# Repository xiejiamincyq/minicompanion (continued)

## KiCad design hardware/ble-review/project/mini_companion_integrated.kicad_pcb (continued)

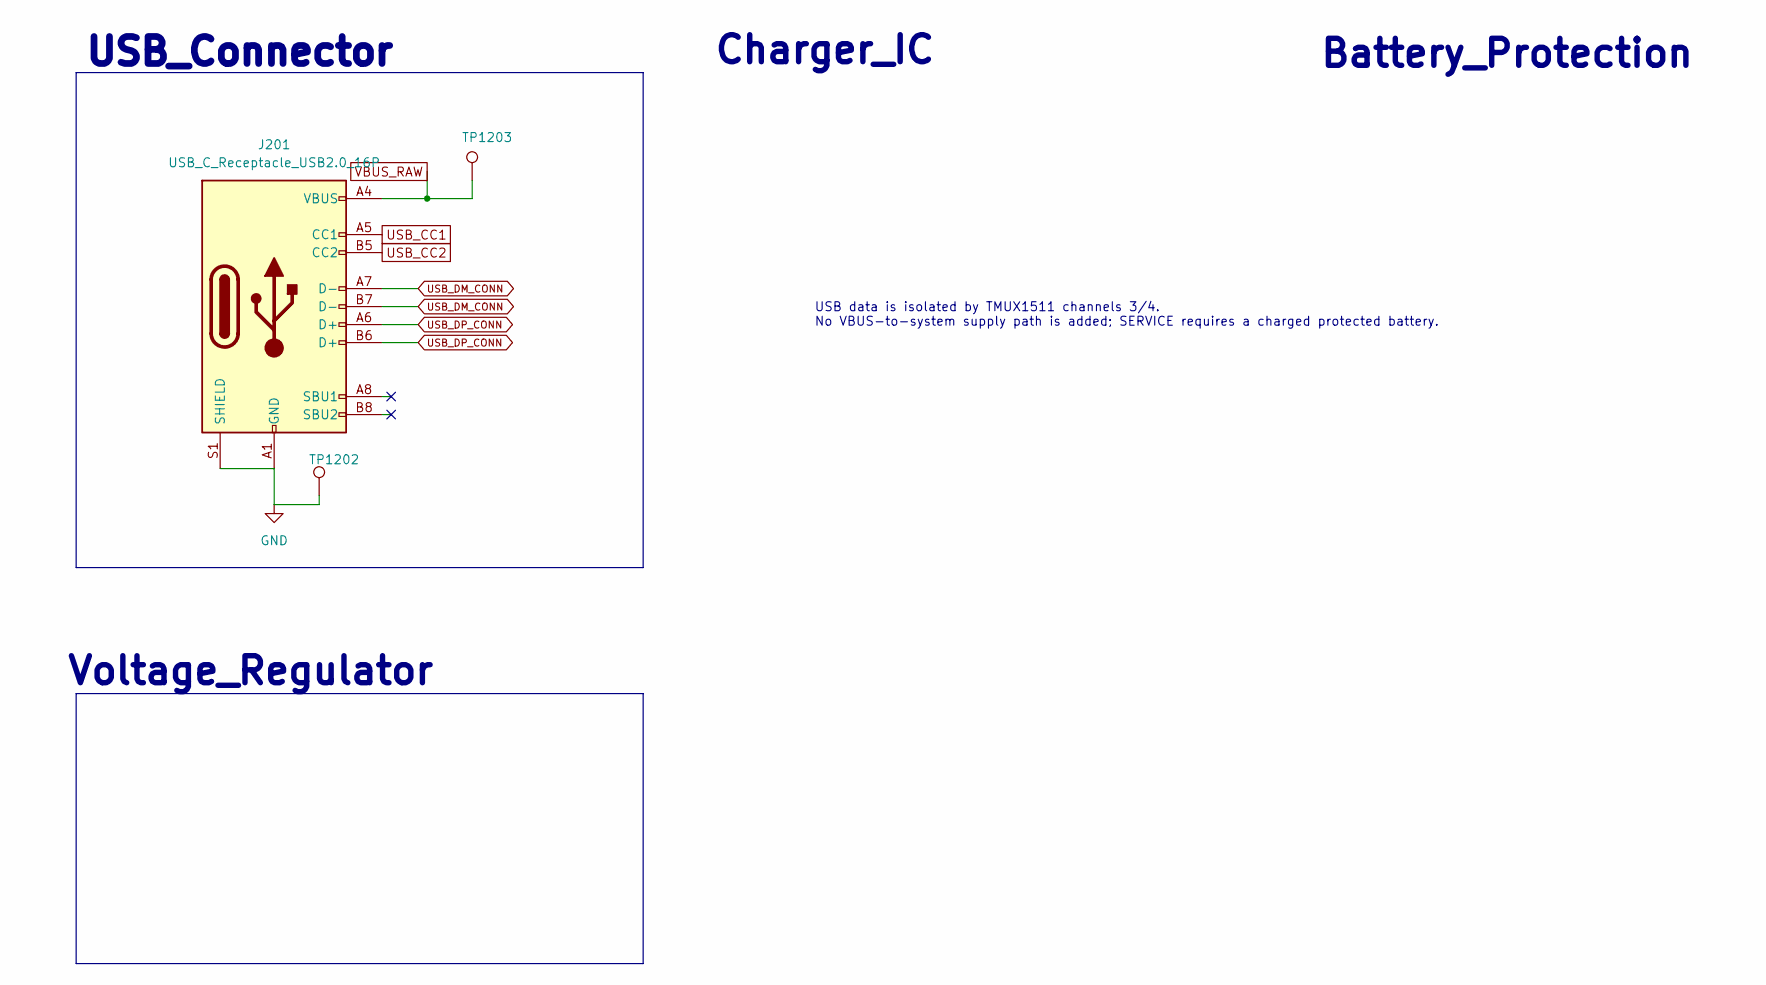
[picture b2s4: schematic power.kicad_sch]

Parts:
J201: USB_C_Receptacle_USB2.0_16P; USB_C_Receptacle_HRO_TYPE-C-31-M-12; LCSC Part C165948
TP1202, TP1203: TestPoint; TestPoint_Pad_D1.0mm

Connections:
GND: J201.A1 (GND), J201.A12 (GND), J201.B1 (GND), J201.B12 (GND), J201.S1 (SHIELD), TP1202.1 (1_1); also elsewhere on the board
USB_CC1: J201.A5 (CC1); also elsewhere on the board
USB_CC2: J201.B5 (CC2); also elsewhere on the board
USB_DM_CONN: J201.A7 (D-), J201.B7 (D-); also elsewhere on the board
USB_DP_CONN: J201.A6 (D+), J201.B6 (D+); also elsewhere on the board
VBUS_RAW: J201.A4 (VBUS), J201.A9 (VBUS), J201.B4 (VBUS), J201.B9 (VBUS), TP1203.1 (1_1); also elsewhere on the board

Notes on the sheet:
Battery_Protection
USB_Connector
Voltage_Regulator
Charger_IC
USB data is isolated by TMUX1511 channels 3/4. No VBUS-to-system supply path is added; SERVICE requires a charged protected battery.

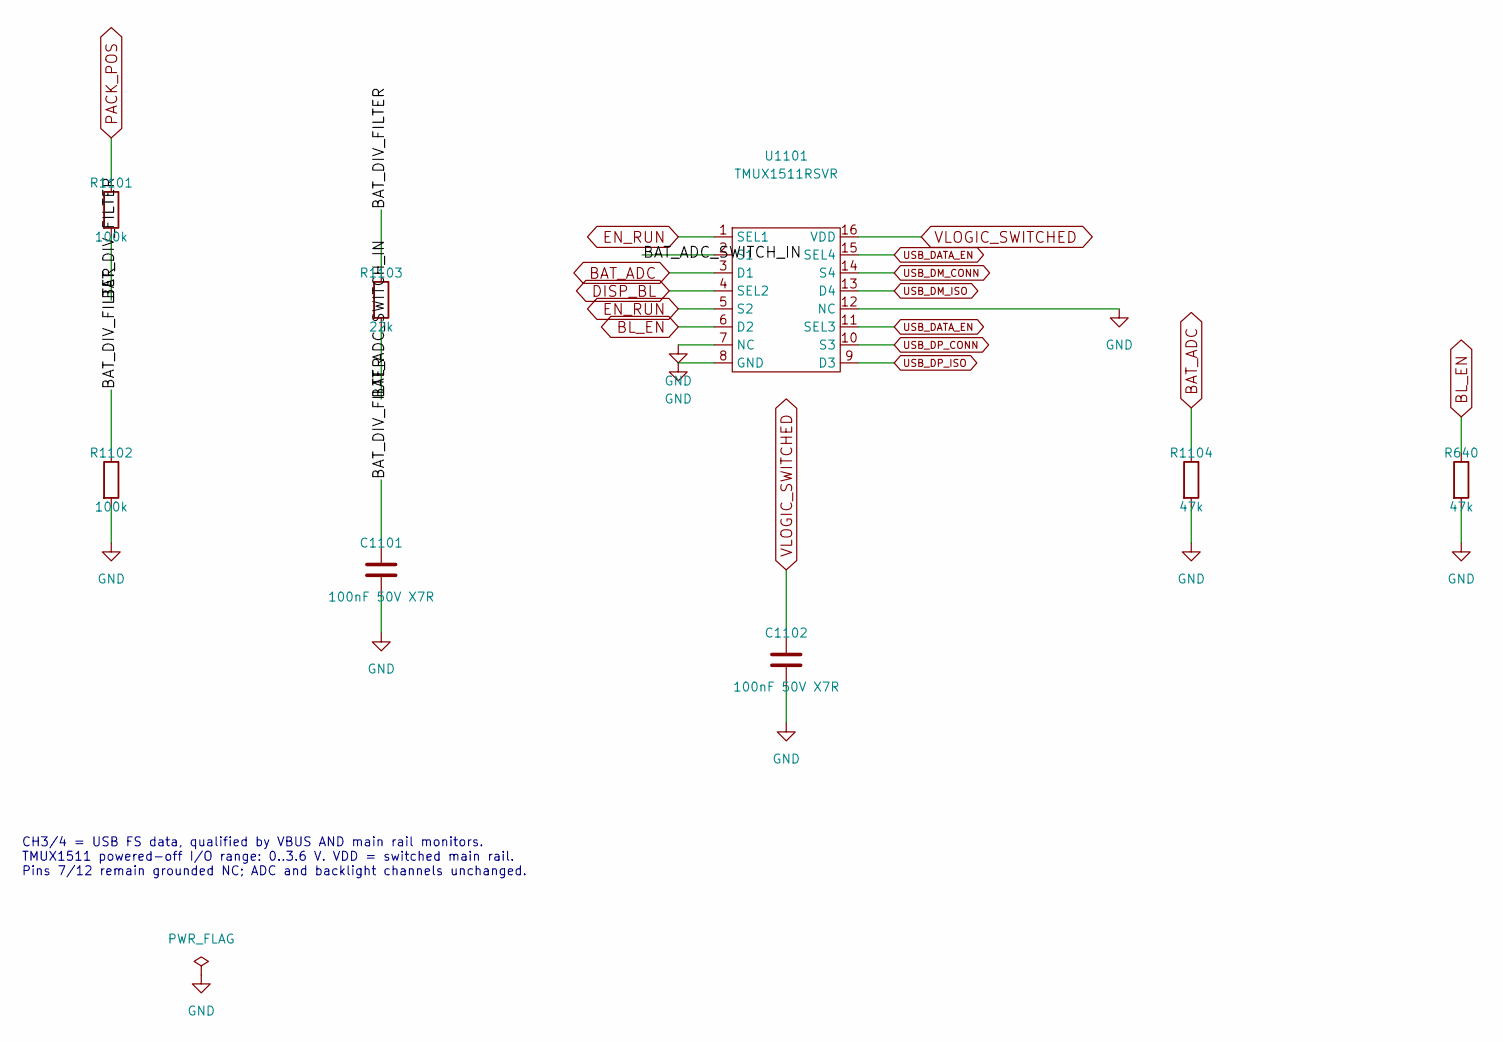
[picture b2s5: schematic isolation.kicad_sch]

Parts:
C1101, C1102: 100nF 50V X7R; C_0603_1608Metric; MPN CC0603KRX7R9BB104; LCSC C14663
R640, R1104: 47k; R_0603_1608Metric; MPN 0603WAF4702T5E; LCSC C25819
R1101, R1102: 100k; R_0603_1608Metric; MPN 0603WAF1003T5E; LCSC C25803
R1103: 22k; R_0603_1608Metric; MPN 0603WAF2202T5E; LCSC C31850
U1101: TMUX1511RSVR; TI_RSV0016A_UQFN16_1.8x2.6mm_P0.4mm_Vendor; MPN TMUX1511RSVR; LCSC C2673275

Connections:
/isolation/BAT_ADC_SWITCH_IN: R1103.2, U1101.2 (S1)
/isolation/BAT_DIV_FILTER: C1101.1, R1101.2, R1102.1, R1103.1
BAT_ADC: R1104.1, U1101.3 (D1); also elsewhere on the board
BL_EN: R640.1, U1101.6 (D2); also elsewhere on the board
DISP_BL: U1101.4 (SEL2); also elsewhere on the board
EN_RUN: U1101.1 (SEL1), U1101.5 (S2); also elsewhere on the board
GND: C1101.2, C1102.2, R640.2, R1102.2, R1104.2, U1101.7 (NC), U1101.8 (GND), U1101.12 (NC); also elsewhere on the board
PACK_POS: R1101.1; also elsewhere on the board
USB_DATA_EN: U1101.11 (SEL3), U1101.15 (SEL4); also elsewhere on the board
USB_DM_CONN: U1101.14 (S4); also elsewhere on the board
USB_DM_ISO: U1101.13 (D4); also elsewhere on the board
USB_DP_CONN: U1101.10 (S3); also elsewhere on the board
USB_DP_ISO: U1101.9 (D3); also elsewhere on the board
VLOGIC_SWITCHED: C1102.1, U1101.16 (VDD); also elsewhere on the board

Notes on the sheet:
CH3/4 = USB FS data, qualified by VBUS AND main rail monitors. TMUX1511 powered-off I/O range: 0..3.6 V. VDD = switched main rail. Pins 7/12 remain grounded NC; ADC and backlight channels unchanged.

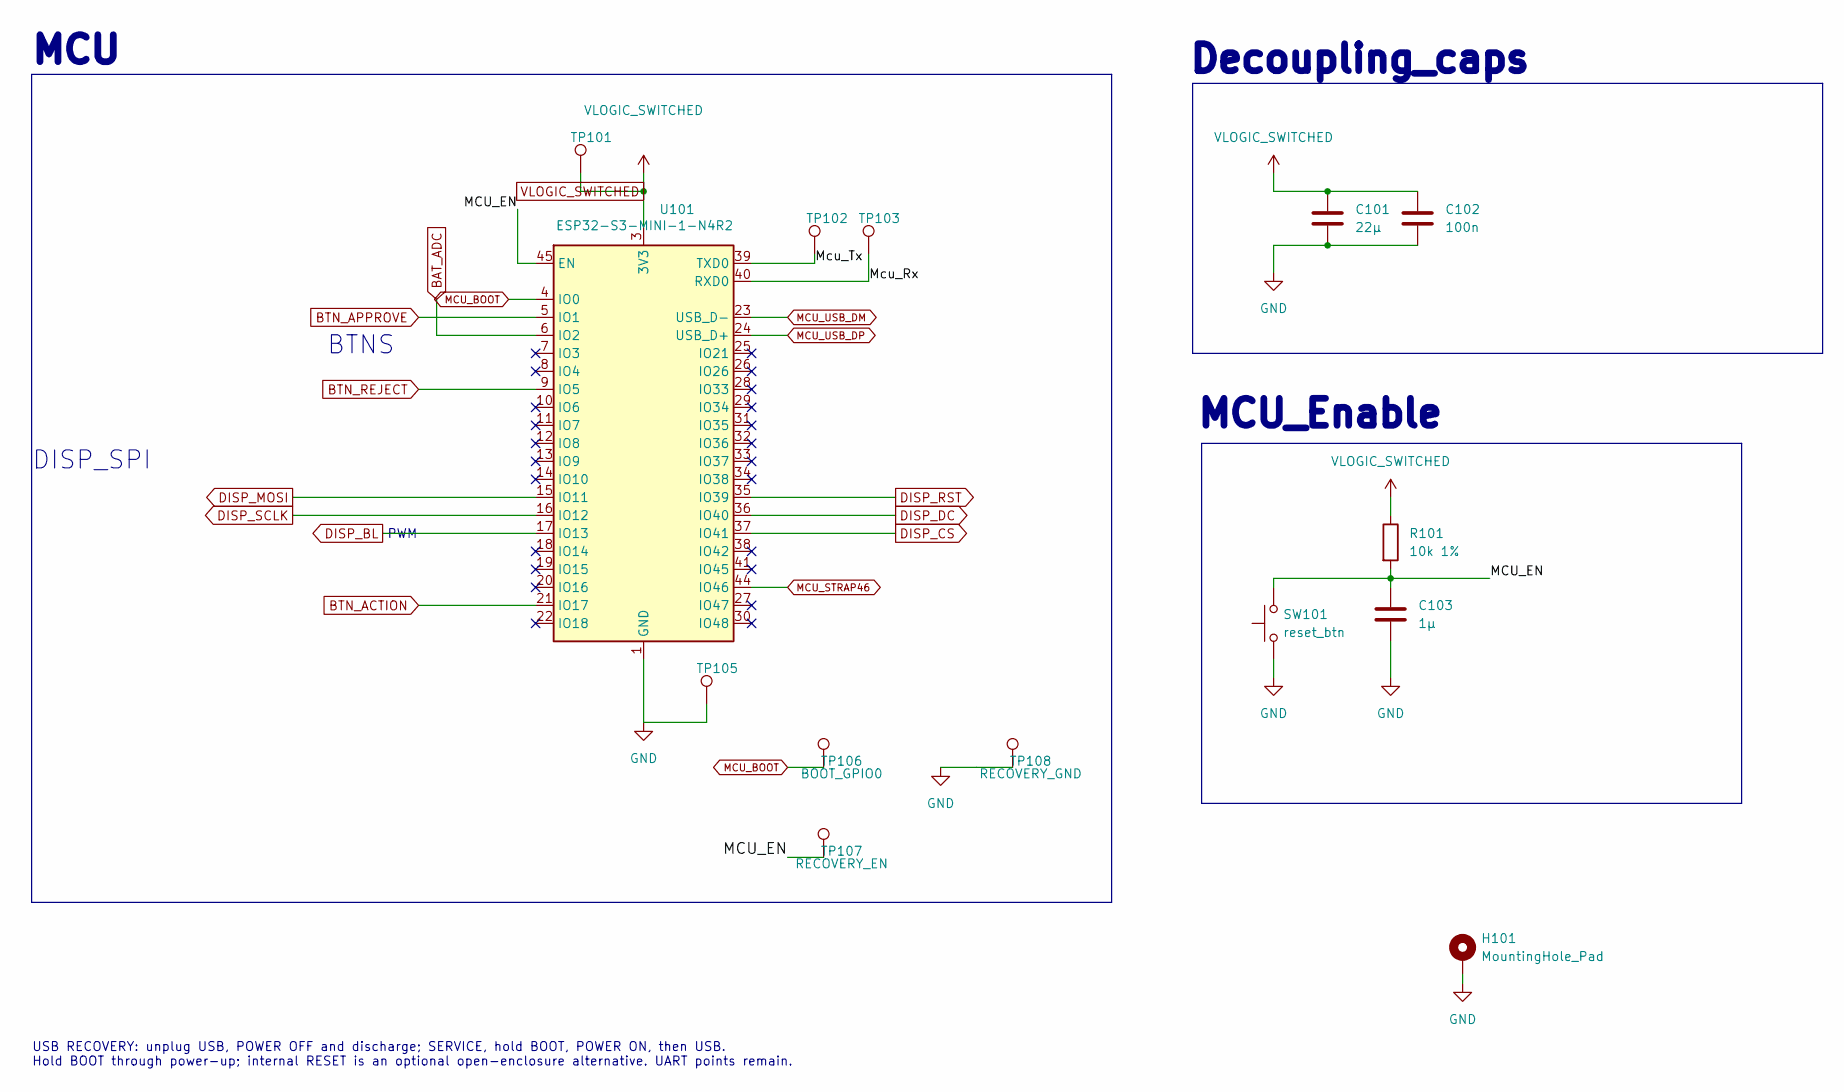
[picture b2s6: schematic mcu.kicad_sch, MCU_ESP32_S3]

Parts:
C101: 22µ; C_0805_2012Metric_Pad1.18x1.45mm_HandSolder; LCSC Part C45783
C102: 100n; C_0603_1608Metric_Pad1.08x0.95mm_HandSolder; LCSC Part C14663
C103: 1µ; C_0603_1608Metric_Pad1.08x0.95mm_HandSolder; LCSC Part C15849
H101: MountingHole_Pad; MountingHole_2.2mm_M2_DIN965_Pad
R101: 10k 1%; R_0603_1608Metric_Pad0.98x0.95mm_HandSolder; LCSC Part C98220
SW101: reset_btn; SW_Push_1P1T_XKB_TS-1187A; LCSC Part C318884
TP101, TP105: TestPoint; TestPoint_Pad_D1.0mm
TP102: Tx; TestPoint_Pad_D1.0mm
TP103: Rx; TestPoint_Pad_D1.0mm
TP106: BOOT_GPIO0; TestPoint_Pad_D1.0mm
TP107: RECOVERY_EN; TestPoint_Pad_D1.0mm
TP108: RECOVERY_GND; TestPoint_Pad_D1.0mm
U101: ESP32-S3-MINI-1-N4R2; ESP32-S3-MINI-1; LCSC Part C3013941

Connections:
/mcu/MCU_EN: C103.1, R101.2, SW101.2, TP107.1 (1_1), U101.45 (EN)
/mcu/Mcu_Rx: TP103.1 (1_1), U101.40 (RXD0)
/mcu/Mcu_Tx: TP102.1 (1_1), U101.39 (TXD0)
BAT_ADC: U101.6 (IO2); also elsewhere on the board
BTN_ACTION: U101.21 (IO17); also elsewhere on the board
BTN_APPROVE: U101.5 (IO1); also elsewhere on the board
BTN_REJECT: U101.9 (IO5); also elsewhere on the board
DISP_BL: U101.17 (IO13); also elsewhere on the board
DISP_CS: U101.37 (IO41); also elsewhere on the board
DISP_DC: U101.36 (IO40); also elsewhere on the board
DISP_MOSI: U101.15 (IO11); also elsewhere on the board
DISP_RST: U101.35 (IO39); also elsewhere on the board
DISP_SCLK: U101.16 (IO12); also elsewhere on the board
GND: C101.2, C102.2, C103.2, H101.1 (1_1), SW101.1, TP105.1 (1_1), TP108.1 (1_1), U101.1 (GND), U101.2 (GND), U101.42 (GND), U101.43 (GND), U101.46 (GND), U101.47 (GND), U101.48 (GND), U101.49 (GND), U101.50 (GND), U101.51 (GND), U101.52 (GND), U101.53 (GND), U101.54 (GND), U101.55 (GND), U101.56 (GND), U101.57 (GND), U101.58 (GND), U101.59 (GND), U101.60 (GND), U101.61 (GND), U101.62 (GND), U101.63 (GND), U101.64 (GND), U101.65 (GND); also elsewhere on the board
MCU_BOOT: TP106.1 (1_1), U101.4 (IO0); also elsewhere on the board
MCU_STRAP46: U101.44 (IO46); also elsewhere on the board
MCU_USB_DM: U101.23 (USB_D-); also elsewhere on the board
MCU_USB_DP: U101.24 (USB_D+); also elsewhere on the board
VLOGIC_SWITCHED: C101.1, C102.1, R101.1, TP101.1 (1_1), U101.3 (3V3); also elsewhere on the board

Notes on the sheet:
BTNS
DISP_SPI
Decoupling_caps
MCU_Enable
PWM
MCU
USB RECOVERY: unplug USB, POWER OFF and discharge; SERVICE, hold BOOT, POWER ON, then USB. Hold BOOT through power-up; internal RESET is an optional open-enclosure alternative. UART points remain.

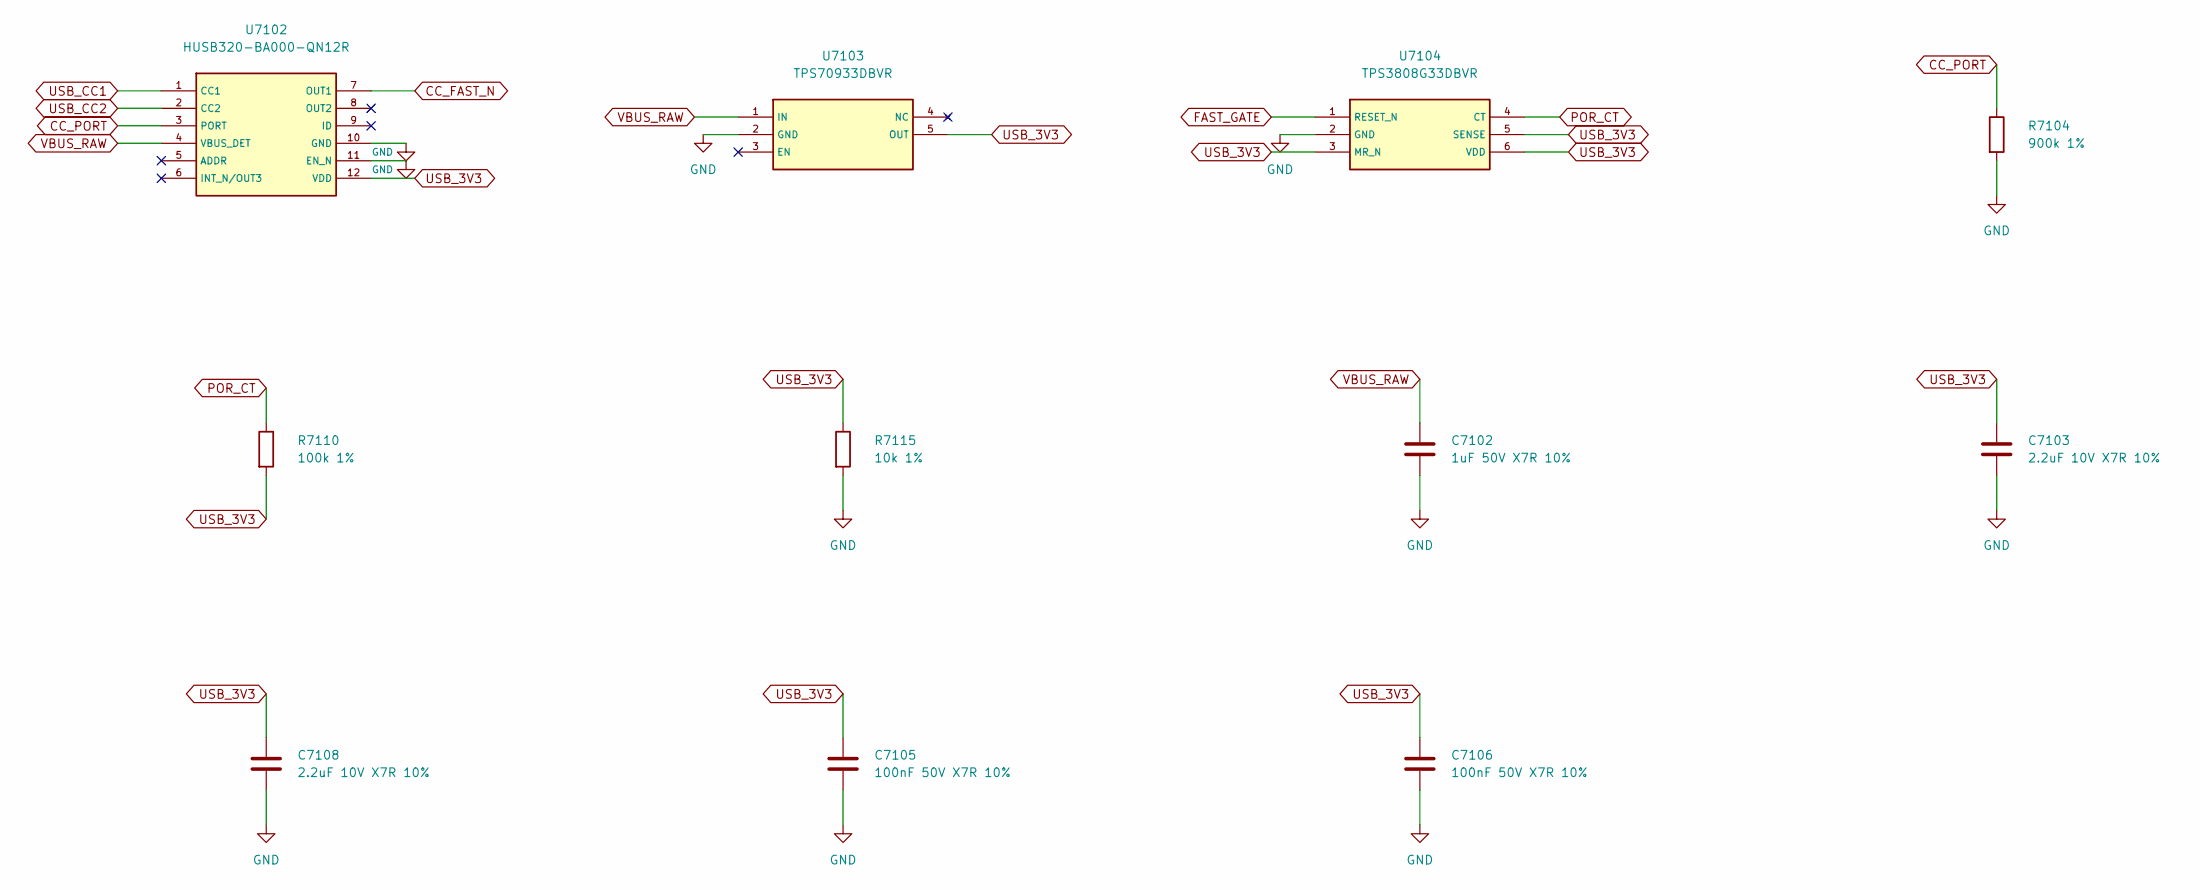
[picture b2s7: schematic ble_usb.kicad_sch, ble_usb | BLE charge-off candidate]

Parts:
C7102: 1uF 50V X7R 10%; C_0805_2012Metric; MPN CL21B105KBFNNNE; LCSC C28323
C7103, C7108: 2.2uF 10V X7R 10%; C_0805_2012Metric; MPN CL21B225KPFNNNE; LCSC C107366
C7105, C7106: 100nF 50V X7R 10%; C_0603_1608Metric; MPN CC0603KRX7R9BB104; LCSC C14663
R7104: 900k 1%; R_0603_1608Metric; MPN RC0603FR-07900KL
R7110: 100k 1%; R_0603_1608Metric; MPN 0603WAF1003T5E; LCSC C25803
R7115: 10k 1%; R_0603_1608Metric; MPN RC0603FR-0710KL
U7102: HUSB320-BA000-QN12R; HUSB320_BA000_Derived_RWB; MPN HUSB320-BA000-QN12R; LCSC C7471906
U7103: TPS70933DBVR; SOT-23-5; MPN TPS70933DBVR; LCSC C89347
U7104: TPS3808G33DBVR; SOT-23-6; MPN TPS3808G33DBVR; LCSC C43698

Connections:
CC_FAST_N: U7102.7 (OUT1); also elsewhere on the board
CC_PORT: R7104.1, U7102.3 (PORT)
FAST_GATE: U7104.1 (RESET_N); also elsewhere on the board
GND: C7102.2, C7103.2, C7105.2, C7106.2, C7108.2, R7104.2, R7115.2, U7102.10 (GND), U7102.11 (EN_N), U7103.2 (GND), U7104.2 (GND); also elsewhere on the board
POR_CT: R7110.1, U7104.4 (CT)
USB_3V3: C7103.1, C7105.1, C7106.1, C7108.1, R7110.2, R7115.1, U7102.12 (VDD), U7103.5 (OUT), U7104.3 (MR_N), U7104.5 (SENSE), U7104.6 (VDD); also elsewhere on the board
USB_CC1: U7102.1 (CC1); also elsewhere on the board
USB_CC2: U7102.2 (CC2); also elsewhere on the board
VBUS_RAW: C7102.1, U7102.4 (VBUS_DET), U7103.1 (IN); also elsewhere on the board

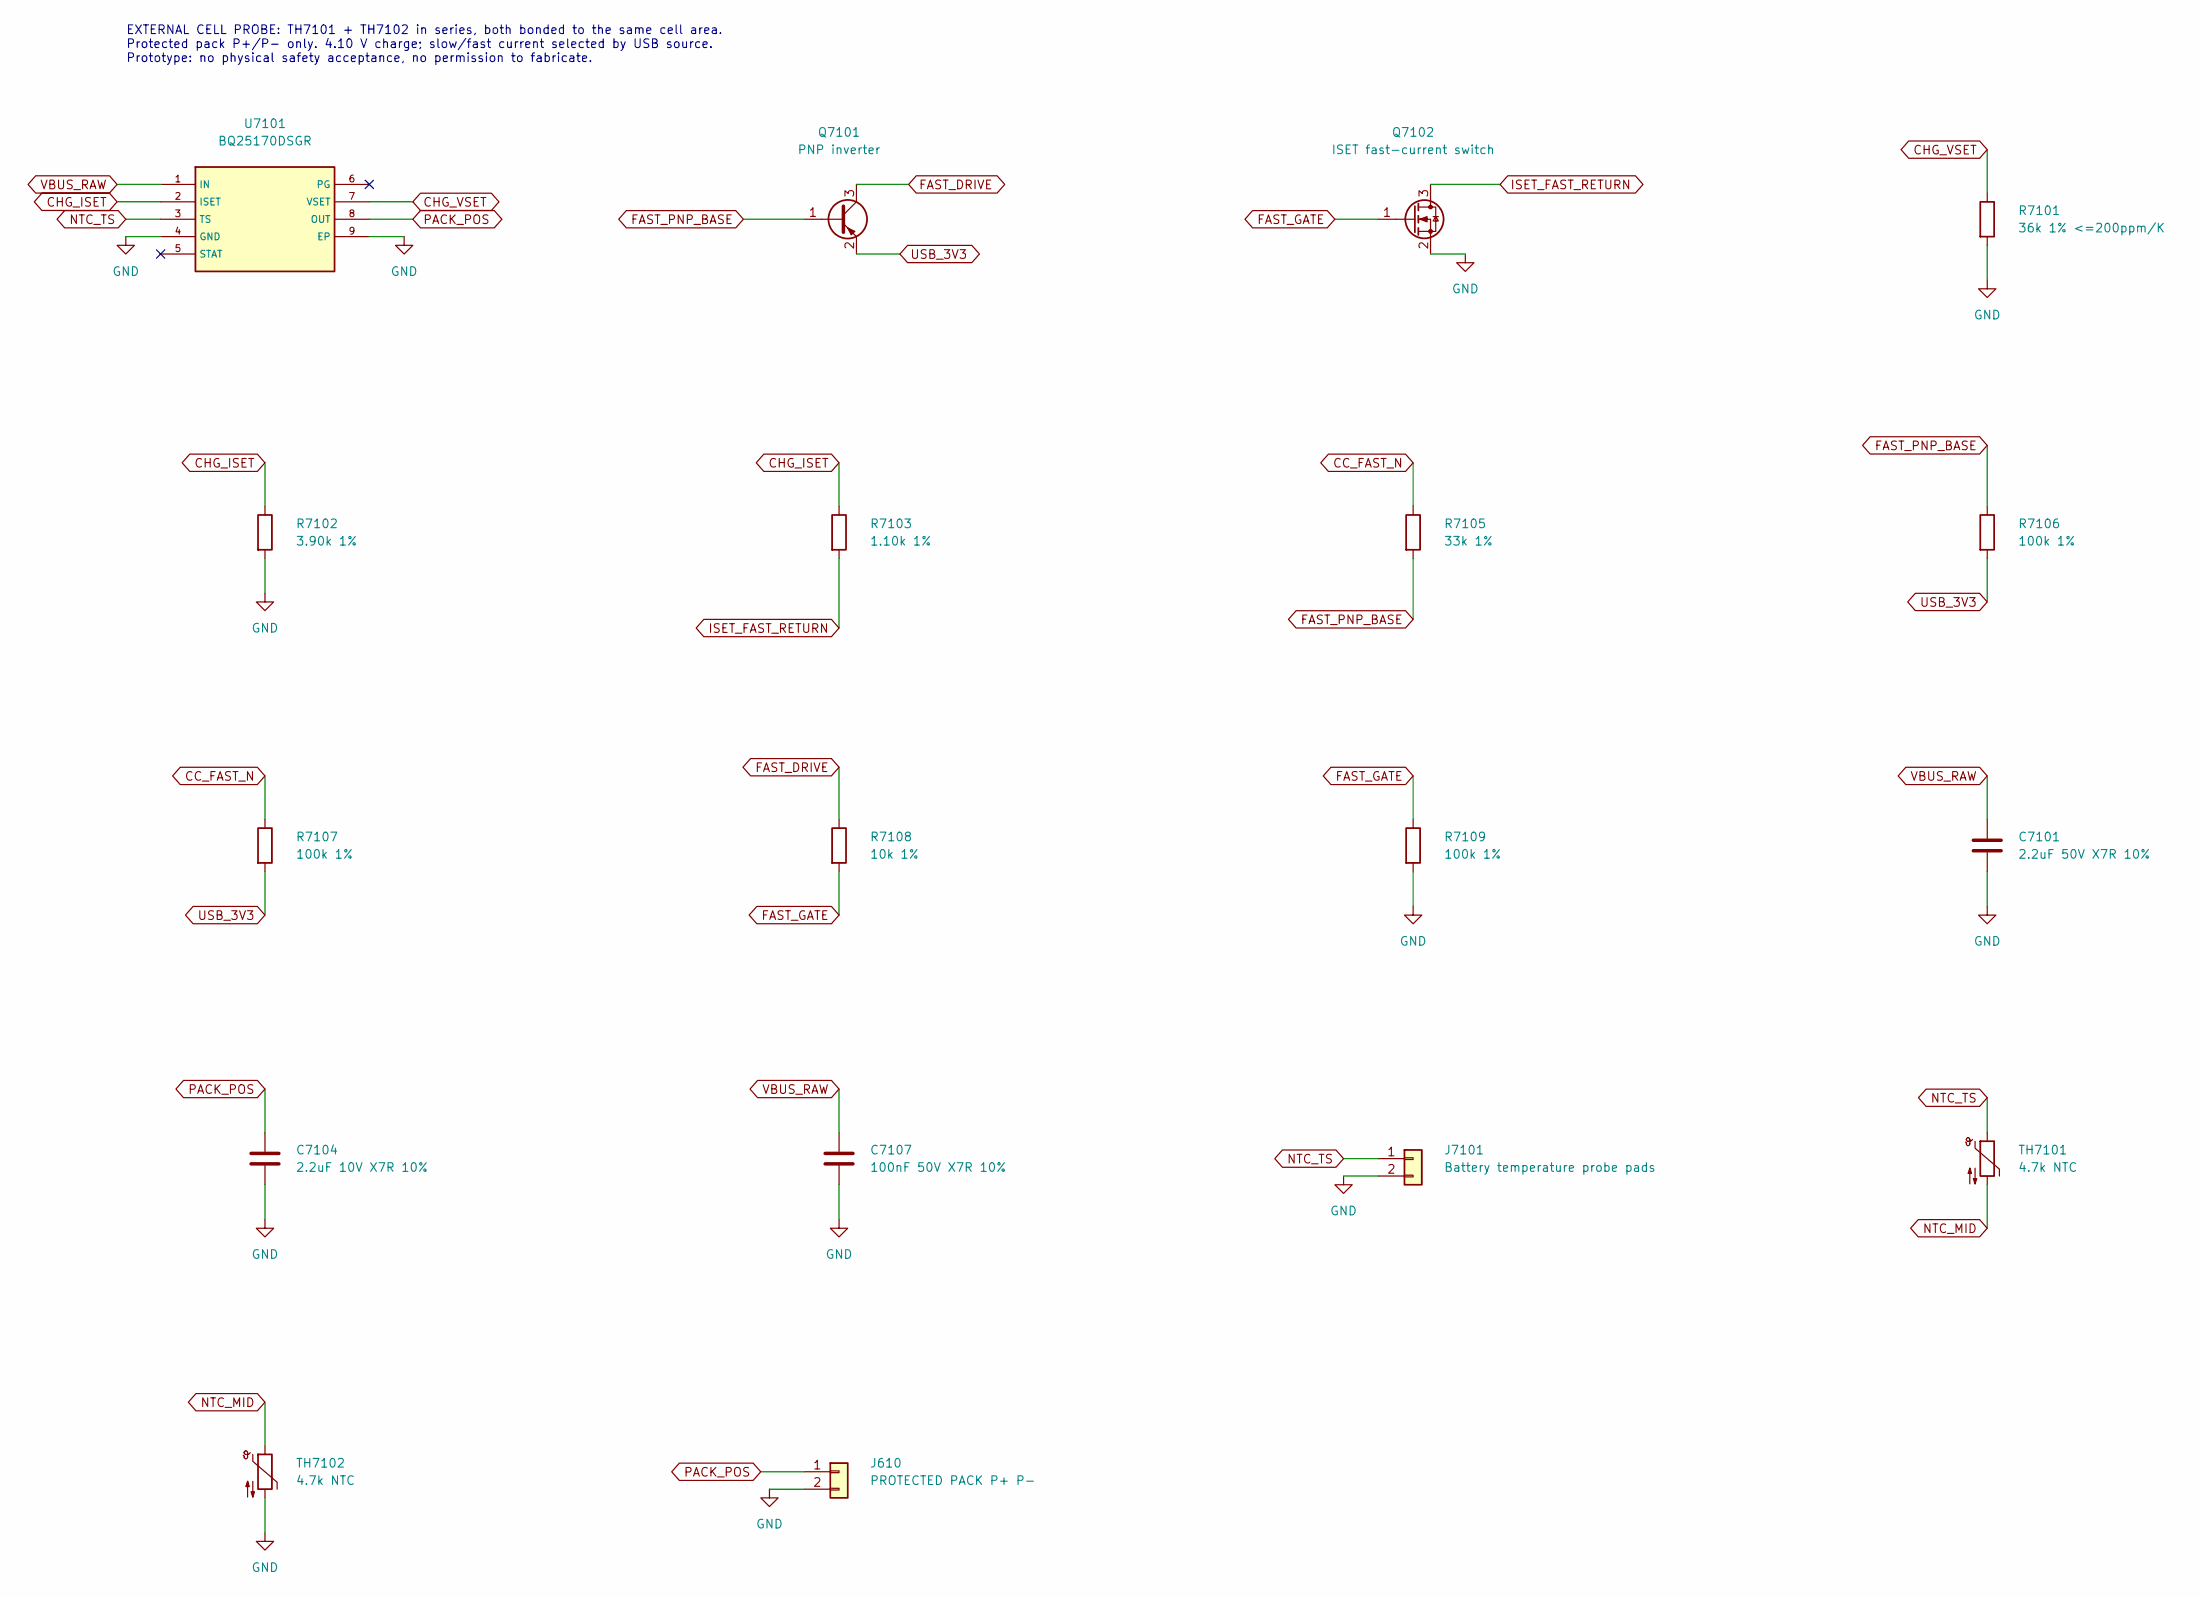
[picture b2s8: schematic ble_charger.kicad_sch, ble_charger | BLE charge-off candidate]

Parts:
C7101: 2.2uF 50V X7R 10%; C_0805_2012Metric; MPN CL21B225KBYNNNE; LCSC C2762602
C7104: 2.2uF 10V X7R 10%; C_0805_2012Metric; MPN CL21B225KPFNNNE; LCSC C107366
C7107: 100nF 50V X7R 10%; C_0603_1608Metric; MPN CC0603KRX7R9BB104; LCSC C14663
J610: PROTECTED PACK P+ P-; WirePads_2_P2.54; MPN SOLDER_PADS_2WIRE
J7101: Battery temperature probe pads; WirePads_2_P2.54; MPN SOLDER_PADS_2WIRE
Q7101: PNP inverter; SOT-23; MPN MMBT3906-7-F; LCSC C82762
Q7102: ISET fast-current switch; SOT-23; MPN AO3400A; LCSC C20917
R7101: 36k 1% <=200ppm/K; R_0603_1608Metric; MPN RC0603FR-0736KL
R7102: 3.90k 1%; R_0603_1608Metric; MPN RC0603FR-073K9L
R7103: 1.10k 1%; R_0603_1608Metric; MPN RC0603FR-071K1L
R7105: 33k 1%; R_0603_1608Metric; MPN RC0603FR-0733KL
R7106, R7107, R7109: 100k 1%; R_0603_1608Metric; MPN 0603WAF1003T5E; LCSC C25803
R7108: 10k 1%; R_0603_1608Metric; MPN RC0603FR-0710KL
TH7101, TH7102: 4.7k NTC; R_0402_1005Metric; MPN ERTJ0ET472H; LCSC C542173
U7101: BQ25170DSGR; Texas_DSG0008A_WSON-8-1EP_2x2mm_P0.5mm_EP0.9x1.6mm; MPN BQ25170DSGR; LCSC C5208201

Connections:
CC_FAST_N: R7105.1, R7107.1; also elsewhere on the board
CHG_ISET: R7102.1, R7103.1, U7101.2 (ISET)
CHG_VSET: R7101.1, U7101.7 (VSET)
FAST_DRIVE: Q7101.3 (C), R7108.1
FAST_GATE: Q7102.1 (G), R7108.2, R7109.1; also elsewhere on the board
FAST_PNP_BASE: Q7101.1 (B), R7105.2, R7106.1
GND: C7101.2, C7104.2, C7107.2, J610.2, J7101.2, Q7102.2 (S), R7101.2, R7102.2, R7109.2, TH7102.2, U7101.4 (GND), U7101.9 (EP); also elsewhere on the board
ISET_FAST_RETURN: Q7102.3 (D), R7103.2
NTC_TS: J7101.1, TH7101.1, U7101.3 (TS); also elsewhere on the board
unnamed: TH7101.2, TH7102.1
PACK_POS: C7104.1, J610.1, U7101.8 (OUT); also elsewhere on the board
USB_3V3: Q7101.2 (E), R7106.2, R7107.2; also elsewhere on the board
VBUS_RAW: C7101.1, C7107.1, U7101.1 (IN); also elsewhere on the board

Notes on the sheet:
EXTERNAL CELL PROBE: TH7101 + TH7102 in series, both bonded to the same cell area. Protected pack P+/P- only. 4.10 V charge; slow/fast current selected by USB source. Prototype: no physical safety acceptance, no permission to fabricate.

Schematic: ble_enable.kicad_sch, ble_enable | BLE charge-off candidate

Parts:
J7201: POWER SWITCH HARNESS; WirePads_3_P2.54; MPN SOLDER_PADS_3WIRE
Q7103: Raw VBUS run inhibit; SOT-23; MPN MMBT3904-7-F
R7111, R7114: 10k 1%; R_0603_1608Metric; MPN RC0603FR-0710KL
R7112: 100k 1%; R_0603_1608Metric; MPN 0603WAF1003T5E; LCSC C25803
R7113: 4.7k 1%; R_0603_1608Metric; MPN RC0603FR-074K7L
SW7201: SS-12D01-G040; MPN SS-12D01-G040; LCSC C2876014

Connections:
EN_RUN: Q7103.3 (C), R7113.2, R7114.1; also elsewhere on the board
GND: J7201.3, Q7103.2 (E), R7112.2, R7114.2; also elsewhere on the board
PACK_POS: J7201.1, SW7201.1 (THROW_ON); also elsewhere on the board
POWER_REQUEST: J7201.2, R7113.1, SW7201.2 (COMMON)
VBUS_INHIBIT_BASE: Q7103.1 (B), R7111.2, R7112.1; also elsewhere on the board
VBUS_RAW: R7111.1; also elsewhere on the board

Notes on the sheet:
SW7201: OFF-BOARD enclosure SPDT switch, pin 2 common. Two insulated leads to J7201; OFF throw is NC. NORMAL: VBUS inhibits EN_RUN; SERVICE exception is on usb_service sheet. Switch mounting, strain relief and power-off timing require physical validation.
POWER HARNESS: TWO WIRES ONLY. J7201.1 -> SW7201 THROW_ON (pin1); J7201.2 -> COMMON (pin2). SW7201 THROW_OFF (pin3) is deliberately unconnected. Insulate unused switch terminal. J7201.3 remains a board GND pad: DO NOT connect it to the power switch. R7114 provides default OFF pull-down when the har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

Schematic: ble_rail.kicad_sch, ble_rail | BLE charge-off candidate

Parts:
C604, C606, C607, C637, C638, C640: 22uF 25V X5R 20%; C_0805_2012Metric; MPN CL21A226MAQNNNE; LCSC C45783
C639: 100nF 50V X7R 10%; C_0603_1608Metric; MPN CC0603KRX7R9BB104; LCSC C14663
L601: 1.5uH 20%, DCR<=42mOhm, Isat7A at20%drop / 25C, I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; Bourns_SRP4020TA; MPN SRP4020TA-1R5M; LCSC C3233727
R603: 953k 0.1% 25ppm/C; R_0603_1608Metric; MPN RT0603BRD07953KL
R607: 180k 0.1% 25ppm/C; R_0603_1608Metric; MPN RT0603BRD07180KL
R608: 10k 1%; R_0603_1608Metric; MPN RC0603FR-0710KL; LCSC C98220
U603: TPS63020DSJR; TI_DSJ0014A_TPS63020; MPN TPS63020DSJR; LCSC C15483

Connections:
EN_RUN: U603.12 (EN); also elsewhere on the board
GND: C604.2, C606.2, C607.2, C637.2, C638.2, C639.2, C640.2, R607.2, R608.2, U603.2 (AGND), U603.15 (PGND_EP); also elsewhere on the board
PACK_POS: C604.1, C638.1, U603.10 (VIN), U603.11 (VIN), U603.13 (PS/SYNC); also elsewhere on the board
SW_L1: L601.1, U603.8 (L1), U603.9 (L1)
SW_L2: L601.2, U603.6 (L2), U603.7 (L2)
VINA_LOCAL: C639.1, U603.1 (VINA)
VLOGIC_FB: R603.2, R607.1, U603.3 (FB)
VLOGIC_SWITCHED: C606.1, C607.1, C637.1, C640.1, R603.1, R608.1, U603.4 (VOUT), U603.5 (VOUT); also elsewhere on the board

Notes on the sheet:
VINA is an INTERNAL regulator output: bypass only; never short it to PACK_POS. Forced PWM. 3.147 V nominal. Six 22 uF capacitors require DC-bias review. DSJ exposed pad: solder and thermal validation required; no via-in-pad assumed.

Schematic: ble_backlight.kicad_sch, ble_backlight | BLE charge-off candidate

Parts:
C617, C620: 2.2uF 10V X7R 10%; C_0805_2012Metric; MPN CL21B225KPFNNNE; LCSC C107366
C618, C619: 470nF 25V X7R 10%; C_0603_1608Metric; MPN CL10B474KA8NNNC; LCSC C1623
R628: 8.06k 1%; R_0603_1608Metric; MPN RC0603FR-078K06L; LCSC C131052
R629: 10k 1%; R_0603_1608Metric; MPN RC0603FR-0710KL; LCSC C98220
U609: TPS60231RGTR; VQFN-16-1EP_3x3mm_P0.5mm_EP1.6x1.6mm; MPN TPS60231RGTR; LCSC C544659

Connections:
BL_C1M: C618.2, U609.11 (C1-)
BL_C1P: C618.1, U609.10 (C1+)
BL_C2M: C619.2, U609.12 (C2-)
BL_C2P: C619.1, U609.9 (C2+)
BL_EN: U609.15 (EN1), U609.16 (EN2); also elsewhere on the board
BL_ISET: R628.1, U609.1 (ISET)
DISP_BL: R629.1; also elsewhere on the board
GND: C617.2, C620.2, R628.2, R629.2, U609.7 (PGND), U609.14 (GND), U609.17 (EP); also elsewhere on the board
LED_A: C620.1, U609.8 (VOUT); also elsewhere on the board
LED_K: U609.4 (D3), U609.5 (D2), U609.6 (D1); also elsewhere on the board
PACK_POS: C617.1, U609.13 (VIN); also elsewhere on the board

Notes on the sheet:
Retain regulated current backlight. Three D outputs paralleled per TI Figure 12. EN1/EN2 isolated from the MCU by U1101; default disabled. Check LED current and removal transients on the actual protected pack.

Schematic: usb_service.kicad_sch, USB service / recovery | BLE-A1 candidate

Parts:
C7301: 100nF 50V; C_0603_1608Metric; MPN CC0603KRX7R9BB104; LCSC C14663
D7301: PESD5V0U2BT,215; SOT-23; MPN PESD5V0U2BT,215; LCSC C85399
R7301, R7306, R7308: 10k 1%; R_0603_1608Metric; MPN 0603WAF1002T5E; LCSC C25804
R7302, R7303: 22R 1%; R_0603_1608Metric; MPN 0603WAF220JT5E; LCSC C23345
R7304: 100k 0.1%; R_0603_1608Metric; MPN RT0603BRD07100KL; LCSC C122538
R7305: 10k 0.1%; R_0603_1608Metric; MPN RT0603BRD0710KL; LCSC C95204
R7307: 100k 1%; R_0603_1608Metric; MPN 0603WAF1003T5E; LCSC C25803
SW7301: SERVICE / NORMAL; CK_JS202011SCQN; MPN JS202011SCQN; LCSC C221666
SW7302: BOOT; SW_Push_1P1T_XKB_TS-1187A; MPN TS-1187A-B-A-B; LCSC C318884
U7301: TPS3808G01DBVR; SOT-23-6; MPN TPS3808G01DBVR; LCSC C19653

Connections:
GND: C7301.2, D7301.3 (COMMON_GND), R7305.2, R7307.2, R7308.2, SW7301.2 (COMMON_A), SW7301.5 (COMMON_B), SW7302.2, U7301.2 (GND); also elsewhere on the board
MCU_BOOT: R7301.2, SW7302.1; also elsewhere on the board
MCU_STRAP46: R7308.1; also elsewhere on the board
MCU_USB_DM: R7303.2; also elsewhere on the board
MCU_USB_DP: R7302.2; also elsewhere on the board
NTC_TS: SW7301.3 (SERVICE_A); also elsewhere on the board
USB_3V3: C7301.1, R7306.1, U7301.3 (MR_N), U7301.6 (VDD); also elsewhere on the board
USB_DATA_EN: R7306.2, R7307.1, U7301.1 (RESET_N); also elsewhere on the board
USB_DM_CONN: D7301.2 (LINE2); also elsewhere on the board
USB_DM_ISO: R7303.1; also elsewhere on the board
USB_DP_CONN: D7301.1 (LINE1); also elsewhere on the board
USB_DP_ISO: R7302.1; also elsewhere on the board
USB_VBUS_SENSE: R7304.2, R7305.1, U7301.5 (SENSE)
VBUS_INHIBIT_BASE: SW7301.6 (SERVICE_B); also elsewhere on the board
VBUS_RAW: R7304.1; also elsewhere on the board
VLOGIC_SWITCHED: R7301.1; also elsewhere on the board

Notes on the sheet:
1. MODE AND RECOVERY
NORMAL: TS probe and VBUS run-inhibit untouched. SERVICE: charging disabled, battery run permitted. Recovery: unplug USB; POWER OFF and discharge; SERVICE; hold BOOT; POWER ON; attach data cable. After use: unplug USB before returning NORMAL. Empty battery: charge in NORMAL first.
2. HARDWARE VBUS QUALIFICATION
R7304/R7305: 0.1% divider, nominal 4.455 V falling threshold. CT open: 12..28 ms release. U7302 on usb_enable_gate also qualifies main rail. Both open-drain monitors must release before DATA_EN can rise.
3. USB FULL-SPEED PATH
J201 -> D7301 -> U1101 CH3/CH4 -> 22 ohm -> MCU GPIO20/19. Place TVS at connector, series resistors at MCU. Keep D+/D- coupled over GND. No bus-power or charging during SERVICE. USB-only recovery with an empty battery is unsupported.

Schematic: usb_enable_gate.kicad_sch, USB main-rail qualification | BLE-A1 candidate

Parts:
C7302: 100nF 50V; C_0603_1608Metric; MPN CC0603KRX7R9BB104; LCSC C14663
R7309: 2.7k 1% 250mW; R_1206_3216Metric; MPN 1206W4F2701T5E; LCSC C17950
R7310: 15.8k 0.1%; R_0603_1608Metric; MPN RT0603BRD0715K8L; LCSC C861143
R7311: 10k 0.1%; R_0603_1608Metric; MPN RT0603BRD0710KL; LCSC C95204
U7302: TPS389001DSER; WSON-6_1.5x1.5mm_P0.5mm; MPN TPS389001DSER; LCSC C1509297

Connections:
GND: C7302.2, R7309.2, R7311.2, U7302.2 (GND); also elsewhere on the board
USB_3V3: C7302.1, U7302.3 (MR), U7302.4 (VDD); also elsewhere on the board
USB_DATA_EN: U7302.6 (RESET); also elsewhere on the board
USB_MAIN_SENSE: R7310.2, R7311.1, U7302.1 (SENSE)
VBUS_RAW: R7309.1; also elsewhere on the board
VLOGIC_SWITCHED: R7310.1; also elsewhere on the board

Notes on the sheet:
1. MAIN RAIL MUST BE PRESENT BEFORE USB DATA CONNECTS
U7302 is supplied by USB_3V3, so VLOGIC_SWITCHED = 0 V cannot float its reset output. R7310/R7311 set a nominal falling trip of 2.967 V. Both resistors: 0.1%, 25 ppm/C. CT deliberately open. RESET is wired-AND with VBUS monitor U7301 on USB_DATA_EN.
2. RAW VBUS DISCHARGE
R7309 limits retained VBUS after cable removal. 1206 / 250 mW required. At 20 V: nominal 148 mW. At 5.5 V: 11.2 mW. Do not substitute 0.1 W 0603. Host source collapse, switch bounce, main-rail dynamics and USB suspend remain sample tests.
DESIGN LIMIT: comparator tolerances and delay do not prove USB compliance or transient safety. Capture DATA_EN, main rail, VBUS and D+/D- on both prototypes before release.
